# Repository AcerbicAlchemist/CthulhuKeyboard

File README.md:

# CthulhuKeyboard
Ortholinear keyboard

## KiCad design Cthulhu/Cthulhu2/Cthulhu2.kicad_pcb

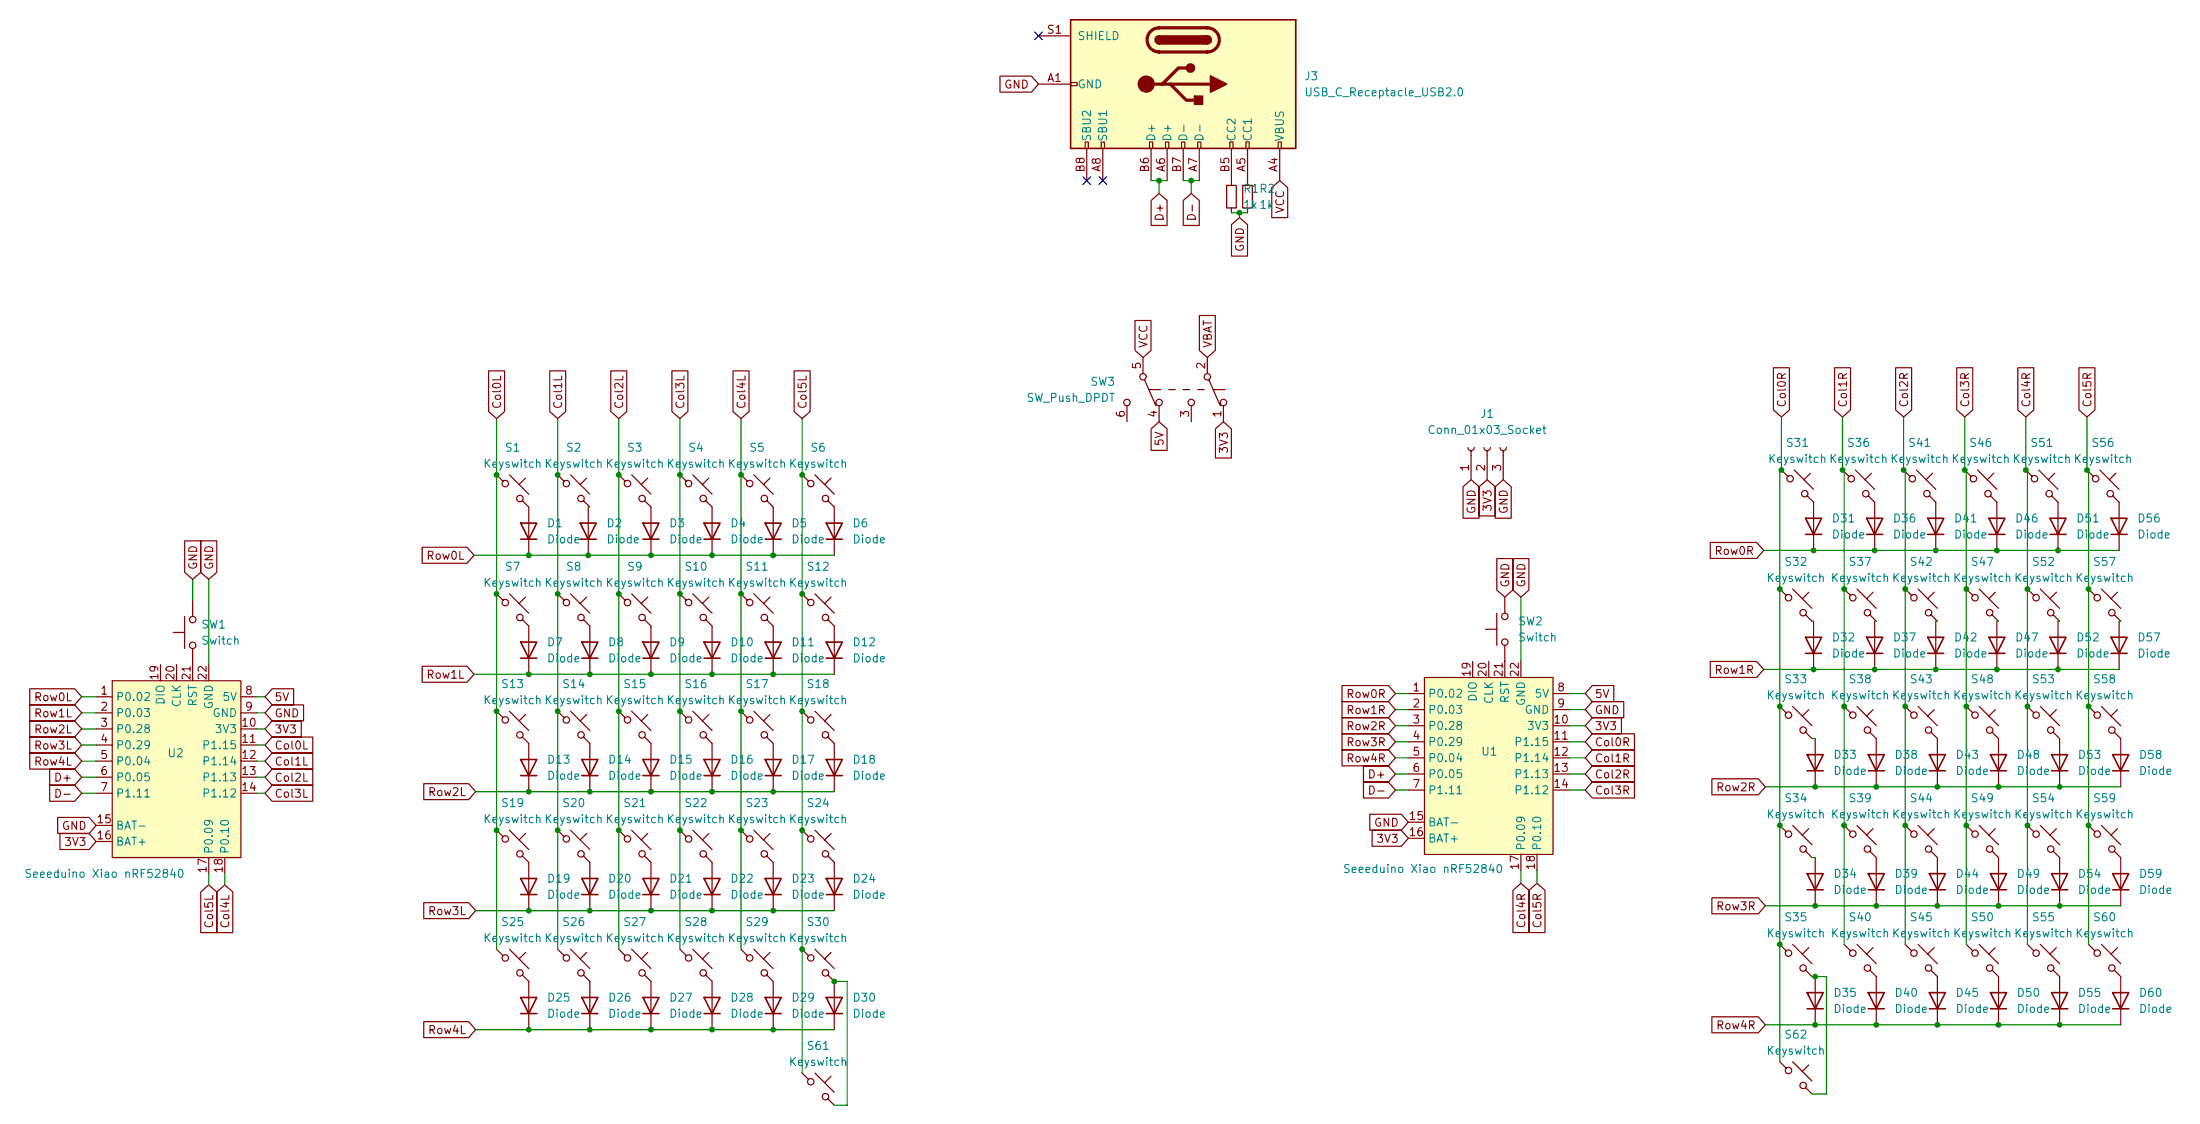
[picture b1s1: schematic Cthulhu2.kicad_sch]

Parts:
D1, D2, D3, D4, D5, D6, D7, D8, D9, D10, D11, D12, D13, D14, D15, D16, D17, D18, D19, D20, D21, D22, D23, D24, D25, D26, D27, D28, D29, D30, D31, D32, D33, D34, D35, D36, D37, D38, D39, D40, D41, D42, D43, D44, D45, D46, D47, D48, D49, D50, D51, D52, D53, D54, D55, D56, D57, D58, D59, D60: Diode; Diode_SOD-123
J1: Conn_01x03_Socket; JST_EH_S3B-EH_1x03_P2.50mm_Horizontal
J3: USB_C_Receptacle_USB2.0; USB_C_Receptacle_HRO_TYPE-C-31-M-12
R1, R2: 1k; R_0805_2012Metric_Pad1.20x1.40mm_HandSolder
S1, S2, S3, S4, S5, S6, S7, S8, S9, S10, S11, S12, S13, S14, S15, S16, S17, S18, S19, S20, S21, S22, S23, S24, S25, S26, S27, S28, S29, S30, S31, S32, S33, S34, S35, S36, S37, S38, S39, S40, S41, S42, S43, S44, S45, S46, S47, S48, S49, S50, S51, S52, S53, S54, S55, S56, S57, S58, S59, S60, S61, S62: Keyswitch; Hotswap_Choc_V1V2_1.00u
SW1, SW2: Switch; Button_Tact_Sqkg
SW3: SW_Push_DPDT; Switch_Toggle_DPDT_SubMini
U1, U2: Seeeduino Xiao nRF52840; Xiao_nRF52840_ACH

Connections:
3V3: J1.2, SW3.1 (A), U1.10 (3V3), U1.16 (BAT+), U2.10 (3V3), U2.16 (BAT+)
5V: SW3.4 (A), U1.8 (5V), U2.8 (5V)
Col0L: S1.1, S7.1, S13.1, S19.1, S25.1, U2.11 (P1.15)
Col0R: S31.1, S32.1, S33.1, S34.1, S35.1, S62.1, U1.11 (P1.15)
Col1L: S2.1, S8.1, S14.1, S20.1, S26.1, U2.12 (P1.14)
Col1R: S36.1, S37.1, S38.1, S39.1, S40.1, U1.12 (P1.14)
Col2L: S3.1, S9.1, S15.1, S21.1, S27.1, U2.13 (P1.13)
Col2R: S41.1, S42.1, S43.1, S44.1, S45.1, U1.13 (P1.13)
Col3L: S4.1, S10.1, S16.1, S22.1, S28.1, U2.14 (P1.12)
Col3R: S46.1, S47.1, S48.1, S49.1, S50.1, U1.14 (P1.12)
Col4L: S5.1, S11.1, S17.1, S23.1, S29.1, U2.18 (P0.10)
Col4R: S51.1, S52.1, S53.1, S54.1, S55.1, U1.17 (P0.09)
Col5L: S6.1, S12.1, S18.1, S24.1, S30.1, S61.1, U2.17 (P0.09)
Col5R: S56.1, S57.1, S58.1, S59.1, S60.1, U1.18 (P0.10)
D+: J3.A6 (D+), J3.B6 (D+), U1.6 (P0.05), U2.6 (P0.05)
D-: J3.A7 (D-), J3.B7 (D-), U1.7 (P1.11), U2.7 (P1.11)
GND: J1.1, J1.3, J3.A1 (GND), J3.A12 (GND), J3.B1 (GND), J3.B12 (GND), R1.2, R2.2, SW1.2, SW2.2, U1.9 (GND), U1.15 (BAT-), U1.22 (GND), U2.9 (GND), U2.15 (BAT-), U2.22 (GND)
unnamed: D1.2 (A), S1.2
unnamed: D2.2 (A), S2.2
unnamed: D3.2 (A), S3.2
unnamed: D4.2 (A), S4.2
unnamed: D5.2 (A), S5.2
unnamed: D6.2 (A), S6.2
unnamed: D7.2 (A), S7.2
unnamed: D8.2 (A), S8.2
unnamed: D9.2 (A), S9.2
unnamed: D10.2 (A), S10.2
unnamed: D11.2 (A), S11.2
unnamed: D12.2 (A), S12.2
unnamed: D13.2 (A), S13.2
unnamed: D14.2 (A), S14.2
unnamed: D15.2 (A), S15.2
unnamed: D16.2 (A), S16.2
unnamed: D17.2 (A), S17.2
unnamed: D18.2 (A), S18.2
unnamed: D19.2 (A), S19.2
unnamed: D20.2 (A), S20.2
unnamed: D21.2 (A), S21.2
unnamed: D22.2 (A), S22.2
unnamed: D23.2 (A), S23.2
unnamed: D24.2 (A), S24.2
unnamed: D25.2 (A), S25.2
unnamed: D26.2 (A), S26.2
unnamed: D27.2 (A), S27.2
unnamed: D28.2 (A), S28.2
unnamed: D29.2 (A), S29.2
unnamed: D30.2 (A), S30.2, S61.2
unnamed: D31.2 (A), S31.2
unnamed: D32.2 (A), S32.2
unnamed: D33.2 (A), S33.2
unnamed: D34.2 (A), S34.2
unnamed: D35.2 (A), S35.2, S62.2
unnamed: D36.2 (A), S36.2
unnamed: D37.2 (A), S37.2
unnamed: D38.2 (A), S38.2
unnamed: D39.2 (A), S39.2
unnamed: D40.2 (A), S40.2
unnamed: D41.2 (A), S41.2
unnamed: D42.2 (A), S42.2
unnamed: D43.2 (A), S43.2
unnamed: D44.2 (A), S44.2
unnamed: D45.2 (A), S45.2
unnamed: D46.2 (A), S46.2
unnamed: D47.2 (A), S47.2
unnamed: D48.2 (A), S48.2
unnamed: D49.2 (A), S49.2
unnamed: D50.2 (A), S50.2
unnamed: D51.2 (A), S51.2
unnamed: D52.2 (A), S52.2
unnamed: D53.2 (A), S53.2
unnamed: D54.2 (A), S54.2
unnamed: D55.2 (A), S55.2
unnamed: D56.2 (A), S56.2
unnamed: D57.2 (A), S57.2
unnamed: D58.2 (A), S58.2
unnamed: D59.2 (A), S59.2
unnamed: D60.2 (A), S60.2
unnamed: J3.A5 (CC1), R2.1
unnamed: J3.B5 (CC2), R1.1
unnamed: SW2.1, U1.21 (RST)
unnamed: SW1.1, U2.21 (RST)
Row0L: D1.1 (K), D2.1 (K), D3.1 (K), D4.1 (K), D5.1 (K), D6.1 (K), U2.1 (P0.02)
Row0R: D31.1 (K), D36.1 (K), D41.1 (K), D46.1 (K), D51.1 (K), D56.1 (K), U1.1 (P0.02)
Row1L: D7.1 (K), D8.1 (K), D9.1 (K), D10.1 (K), D11.1 (K), D12.1 (K), U2.2 (P0.03)
Row1R: D32.1 (K), D37.1 (K), D42.1 (K), D47.1 (K), D52.1 (K), D57.1 (K), U1.2 (P0.03)
Row2L: D13.1 (K), D14.1 (K), D15.1 (K), D16.1 (K), D17.1 (K), D18.1 (K), U2.3 (P0.28)
Row2R: D33.1 (K), D38.1 (K), D43.1 (K), D48.1 (K), D53.1 (K), D58.1 (K), U1.3 (P0.28)
Row3L: D19.1 (K), D20.1 (K), D21.1 (K), D22.1 (K), D23.1 (K), D24.1 (K), U2.4 (P0.29)
Row3R: D34.1 (K), D39.1 (K), D44.1 (K), D49.1 (K), D54.1 (K), D59.1 (K), U1.4 (P0.29)
Row4L: D25.1 (K), D26.1 (K), D27.1 (K), D28.1 (K), D29.1 (K), D30.1 (K), U2.5 (P0.04)
Row4R: D35.1 (K), D40.1 (K), D45.1 (K), D50.1 (K), D55.1 (K), D60.1 (K), U1.5 (P0.04)
VBAT: SW3.2 (B)
VCC: J3.A4 (VBUS), J3.A9 (VBUS), J3.B4 (VBUS), J3.B9 (VBUS), SW3.5 (B)

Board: 2 copper layers, 131 parts (0 on the bottom side), 92 nets, no tracks yet.

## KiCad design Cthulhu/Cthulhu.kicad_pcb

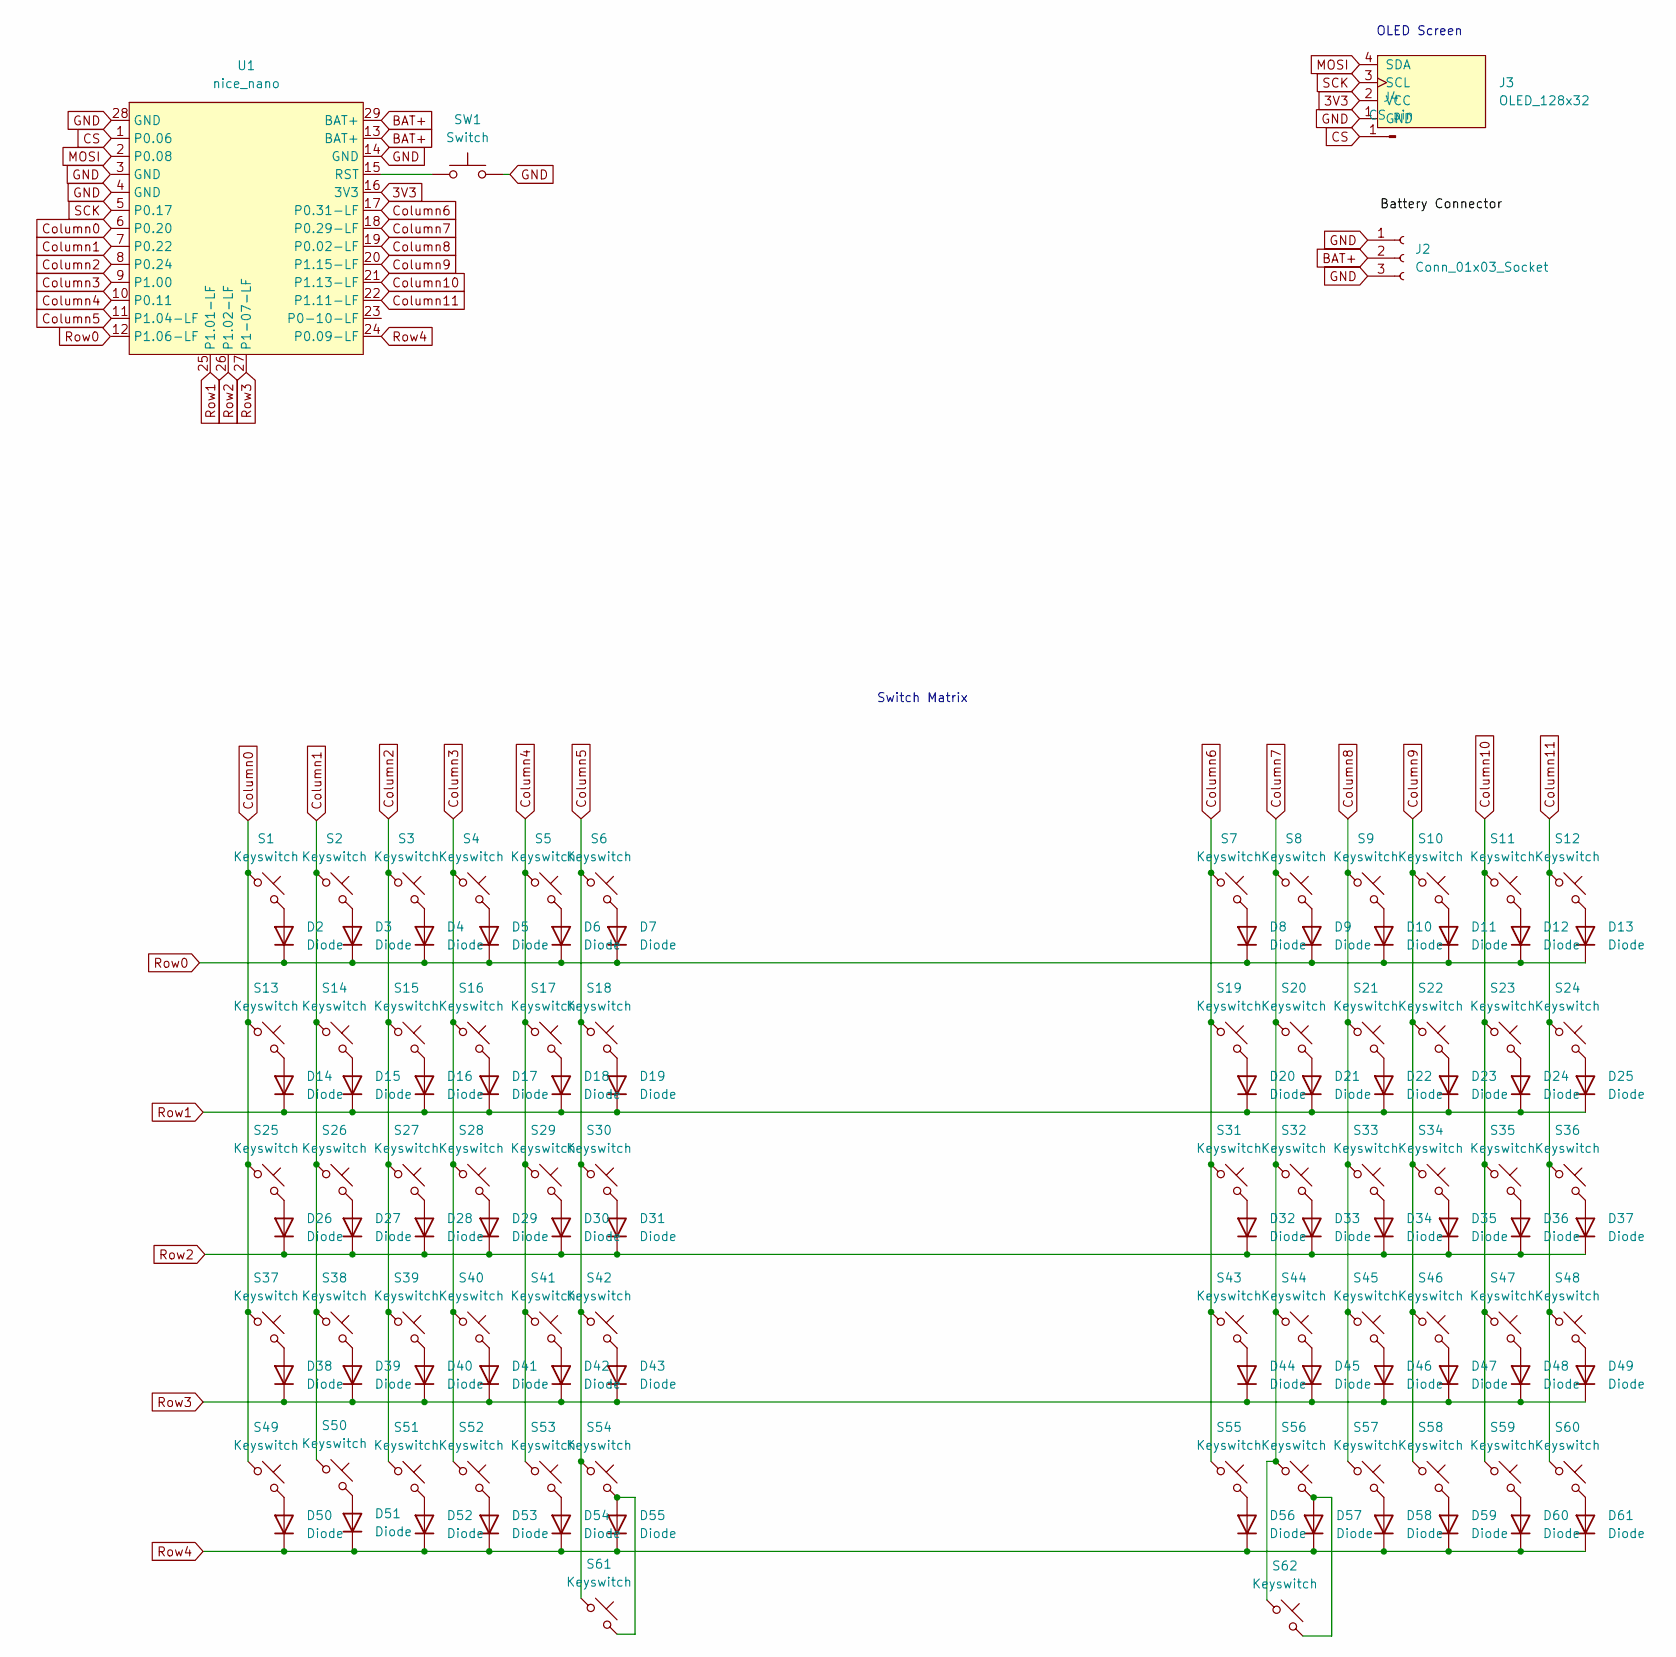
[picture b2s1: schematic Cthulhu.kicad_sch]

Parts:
D2, D3, D4, D5, D6, D7, D8, D9, D10, D11, D12, D13, D14, D15, D16, D17, D18, D19, D20, D21, D22, D23, D24, D25, D26, D27, D28, D29, D30, D31, D32, D33, D34, D35, D36, D37, D38, D39, D40, D41, D42, D43, D44, D45, D46, D47, D48, D49, D50, D51, D52, D53, D54, D55, D56, D57, D58, D59, D60, D61: Diode; Diode_SOD-123
J2: Conn_01x03_Socket; JST_EH_S3B-EH_1x03_P2.50mm_Horizontal
J3: OLED_128x32
J4: CS pin; TestPoint_Bridge_Pitch2.54mm_Drill1.0mm
S1, S2, S3, S4, S5, S6, S7, S8, S9, S10, S11, S12, S13, S14, S15, S16, S17, S18, S19, S20, S21, S22, S23, S24, S25, S26, S27, S28, S29, S30, S31, S32, S33, S34, S35, S36, S37, S38, S39, S40, S41, S42, S43, S44, S45, S46, S47, S48, S49, S50, S51, S52, S53, S54, S55, S56, S57, S58, S59, S60: Keyswitch; MX_Alps_Choc
S61, S62: Keyswitch; MX_PCB_200B
SW1: Switch; Button_Tact_Sqkg
U1: nice_nano; nice_nano_AH_USBup

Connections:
3V3: J3.2 (VCC), U1.16 (3V3)
BAT+: J2.2, U1.13 (BAT+), U1.29 (BAT+)
CS: J4.1, U1.1 (P0.06)
Column0: S1.1, S13.1, S25.1, S37.1, S49.1, U1.6 (P0.20)
Column1: S2.1, S14.1, S26.1, S38.1, S50.1, U1.7 (P0.22)
Column2: S3.1, S15.1, S27.1, S39.1, S51.1, U1.8 (P0.24)
Column3: S4.1, S16.1, S28.1, S40.1, S52.1, U1.9 (P1.00)
Column4: S5.1, S17.1, S29.1, S41.1, S53.1, U1.10 (P0.11)
Column5: S6.1, S18.1, S30.1, S42.1, S54.1, S61.1, U1.11 (P1.04-LF)
Column6: S7.1, S19.1, S31.1, S43.1, S55.1, U1.17 (P0.31-LF)
Column7: S8.1, S20.1, S32.1, S44.1, S56.1, S62.1, U1.18 (P0.29-LF)
Column8: S9.1, S21.1, S33.1, S45.1, S57.1, U1.19 (P0.02-LF)
Column9: S10.1, S22.1, S34.1, S46.1, S58.1, U1.20 (P1.15-LF)
Column10: S11.1, S23.1, S35.1, S47.1, S59.1, U1.21 (P1.13-LF)
Column11: S12.1, S24.1, S36.1, S48.1, S60.1, U1.22 (P1.11-LF)
GND: J2.1, J2.3, J3.1 (GND), SW1.2, U1.4 (GND), U1.14 (GND), U1.28 (GND)
MOSI: J3.4 (SDA), U1.2 (P0.08)
unnamed: D2.2 (A), S1.2
unnamed: D3.2 (A), S2.2
unnamed: D4.2 (A), S3.2
unnamed: D5.2 (A), S4.2
unnamed: D6.2 (A), S5.2
unnamed: D7.2 (A), S6.2
unnamed: D8.2 (A), S7.2
unnamed: D9.2 (A), S8.2
unnamed: D10.2 (A), S9.2
unnamed: D11.2 (A), S10.2
unnamed: D12.2 (A), S11.2
unnamed: D13.2 (A), S12.2
unnamed: D14.2 (A), S13.2
unnamed: D15.2 (A), S14.2
unnamed: D16.2 (A), S15.2
unnamed: D17.2 (A), S16.2
unnamed: D18.2 (A), S17.2
unnamed: D19.2 (A), S18.2
unnamed: D20.2 (A), S19.2
unnamed: D21.2 (A), S20.2
unnamed: D22.2 (A), S21.2
unnamed: D23.2 (A), S22.2
unnamed: D24.2 (A), S23.2
unnamed: D25.2 (A), S24.2
unnamed: D26.2 (A), S25.2
unnamed: D27.2 (A), S26.2
unnamed: D28.2 (A), S27.2
unnamed: D29.2 (A), S28.2
unnamed: D30.2 (A), S29.2
unnamed: D31.2 (A), S30.2
unnamed: D32.2 (A), S31.2
unnamed: D33.2 (A), S32.2
unnamed: D34.2 (A), S33.2
unnamed: D35.2 (A), S34.2
unnamed: D36.2 (A), S35.2
unnamed: D37.2 (A), S36.2
unnamed: D38.2 (A), S37.2
unnamed: D39.2 (A), S38.2
unnamed: D40.2 (A), S39.2
unnamed: D41.2 (A), S40.2
unnamed: D42.2 (A), S41.2
unnamed: D43.2 (A), S42.2
unnamed: D44.2 (A), S43.2
unnamed: D45.2 (A), S44.2
unnamed: D46.2 (A), S45.2
unnamed: D47.2 (A), S46.2
unnamed: D48.2 (A), S47.2
unnamed: D49.2 (A), S48.2
unnamed: D50.2 (A), S49.2
unnamed: D51.2 (A), S50.2
unnamed: D52.2 (A), S51.2
unnamed: D53.2 (A), S52.2
unnamed: D54.2 (A), S53.2
unnamed: D55.2 (A), S54.2, S61.2
unnamed: D56.2 (A), S55.2
unnamed: D57.2 (A), S56.2, S62.2
unnamed: D58.2 (A), S57.2
unnamed: D59.2 (A), S58.2
unnamed: D60.2 (A), S59.2
unnamed: D61.2 (A), S60.2
unnamed: SW1.1, U1.15 (RST)
Row0: D2.1 (K), D3.1 (K), D4.1 (K), D5.1 (K), D6.1 (K), D7.1 (K), D8.1 (K), D9.1 (K), D10.1 (K), D11.1 (K), D12.1 (K), D13.1 (K)
Row1: D14.1 (K), D15.1 (K), D16.1 (K), D17.1 (K), D18.1 (K), D19.1 (K), D20.1 (K), D21.1 (K), D22.1 (K), D23.1 (K), D24.1 (K), D25.1 (K), U1.25 (P1.01-LF)
Row2: D26.1 (K), D27.1 (K), D28.1 (K), D29.1 (K), D30.1 (K), D31.1 (K), D32.1 (K), D33.1 (K), D34.1 (K), D35.1 (K), D36.1 (K), D37.1 (K), U1.26 (P1.02-LF)
Row3: D38.1 (K), D39.1 (K), D40.1 (K), D41.1 (K), D42.1 (K), D43.1 (K), D44.1 (K), D45.1 (K), D46.1 (K), D47.1 (K), D48.1 (K), D49.1 (K), U1.27 (P1-07-LF)
Row4: D50.1 (K), D51.1 (K), D52.1 (K), D53.1 (K), D54.1 (K), D55.1 (K), D56.1 (K), D57.1 (K), D58.1 (K), D59.1 (K), D60.1 (K), D61.1 (K), U1.24 (P0.09-LF)
SCK: J3.3 (SCL), U1.5 (P0.17)

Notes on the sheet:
OLED Screen
Switch Matrix

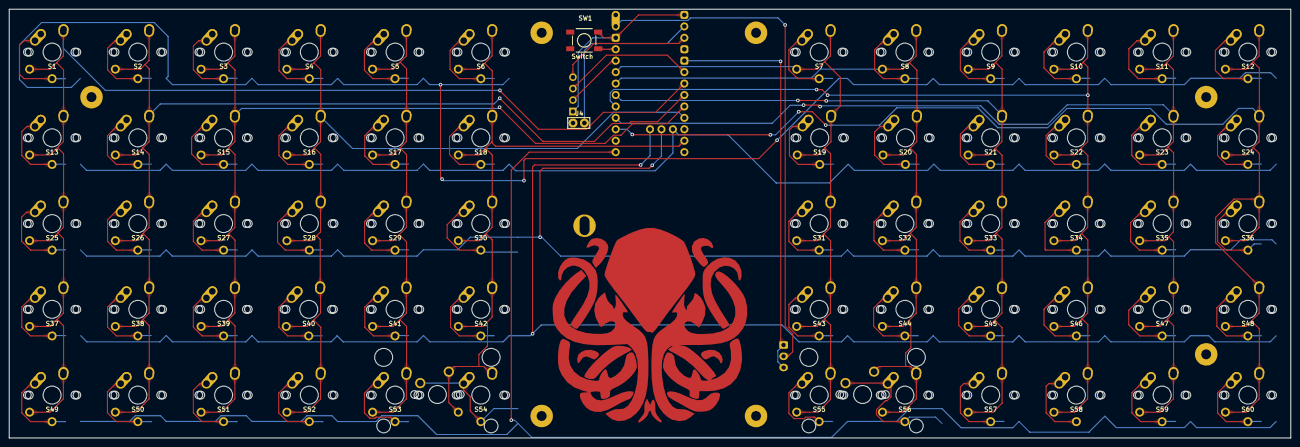
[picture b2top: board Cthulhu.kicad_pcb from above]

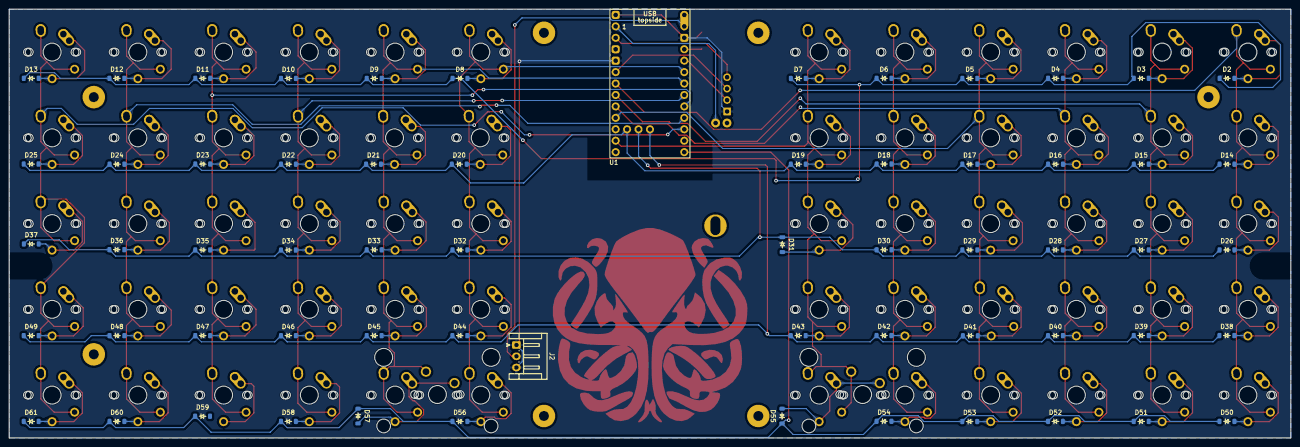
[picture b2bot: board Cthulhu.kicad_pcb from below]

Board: 2 copper layers, 284.7 x 95.2 mm, 127 parts (62 on the bottom side), 84 nets.

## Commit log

2023-11-13 Add files via upload
    Adding keyboard to git
